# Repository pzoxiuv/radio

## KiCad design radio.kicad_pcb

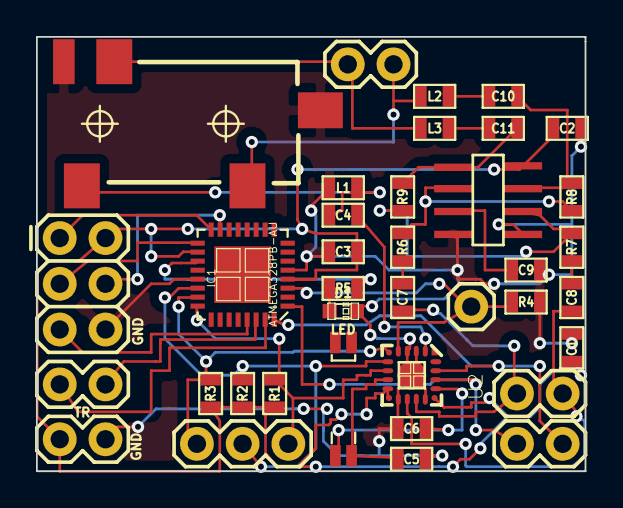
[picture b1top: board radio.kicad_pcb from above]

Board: 2 copper layers, 30.5 x 24.1 mm, 37 parts (0 on the bottom side), 33 nets.

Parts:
C1, C2, C9: .1uF; SM0603
C3: 22nF; SM0603
C4: 1nF; SM0603
C5, C6: 22pF; SM0603
C7, C8: 1uF; SM0603
C10, C11: 47uF; SM0603
D1: LED; LED-0603
IC1: ATMEGA328PB-AU; SparkFun-QFN-32
K1: CONN_3; SparkFun-1X03
L1: 270nH; SM0603
L2, L3: Ferrite 2.5k; SM0603
M1: AUDIO-JACK2; SparkFun-AUDIO-JACK-3.5MM-SMD
P1, P3, P4, P6, P7: CONN_2; SparkFun-1X02
P2: CONN_1; SparkFun-1X01
P5: CONN_3X2; SparkFun-2X3
R1, R2, R3, R4: 10k; SM0603
R5: 1k; SM0603
R6, R7, R8, R9: 20k; SM0603
U2: SI470X; SparkFun-SI470X
U3: TPA6111; tpa6111
X1: 32.768kHz; SparkFun-CRYSTAL-32KHZ-SMD_EPSON_MC146

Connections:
+3.3V: C1.1, C2.1, C3.1, IC1.4, IC1.18, P4.1, P5.2, R1.1, R2.1, R3.1, U2.10, U2.11, U2.16, U3.8
/AVR_RST: IC1.29, P5.5
/GPIO1: IC1.32, P6.2, U2.19
/GPIO2: IC1.1, P6.1, U2.18
/LA: L2.2, M1.TIP, P1.2
/LOUT: C7.1, P7.2, U2.14
/MISO: IC1.16, P5.1
/MOSI: IC1.15, P5.4
/RA: L3.2, M1.RING, P1.1
/ROUT: C8.1, P7.1, U2.13
/RST: IC1.3, P2.1, R4.2, U2.5
/RX: IC1.30, P3.1
/SCK: IC1.17, P5.3
/SCLK: IC1.22, K1.2, R2.2, U2.7
/SDIO: IC1.24, K1.1, R1.2, U2.8
/SEN: IC1.23, K1.3, R3.2, U2.6
/TX: IC1.31, P3.2
GND: C1.2, C2.2, C3.2, C5.2, C6.2, C9.2, D1.2, IC1.5, IC1.21, L1.2, M1.RSH, M1.TSH, P4.2, P5.6, R4.1, U2.3, U2.4, U2.12, U2.15, U2.21, U3.4, U3.5
unnamed: C8.2, R7.1
unnamed: C7.2, R6.1
unnamed: C11.2, L3.1
unnamed: C11.1, R9.2, U3.1
unnamed: C10.2, L2.1
unnamed: C10.1, R8.2, U3.7
unnamed: IC1.19, R5.1
unnamed: C4.1, L1.1, M1.SLEE
unnamed: C4.2, U2.2
unnamed: D1.1, R5.2
unnamed: C6.1, U2.17, X1.2
unnamed: C5.1, U2.9, X1.1
unnamed: C9.1, U3.3
unnamed: R7.2, R9.1, U3.6
unnamed: R6.2, R8.1, U3.2

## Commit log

2017-02-12 Initial commit.
